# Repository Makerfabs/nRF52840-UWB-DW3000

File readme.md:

# Makerfabs nRF52840 UWB DW3000

**The DW3000 library in this repository was developed by NConcepts, not Makerfabs.  Makerfabs is simply responsible for maintaining the repository.**

## 1.Intruduce

Product Link ：[nRF52840 UWB DW3000](https://www.makerfabs.com/nrf52840-uwb-dw3000.html) 

Wiki Link : [nRF52840 UWB DW3000](https://wiki.makerfabs.com/nRF52840%20DW3000%20UWB.html)

Usage : [one-anchor--one-tag](https://github.com/Makerfabs/nRF52840-UWB-DW3000#31-one-anchor--one-tag)

[multi-anchor--multi-tag](https://github.com/Makerfabs/nRF52840-UWB-DW3000#32-multi-anchor--multi-tag)

## 2.Feature

- Controller: nRF52840, 64 MHz Cortex-M4 with FPU, 1 MB Flash, 256 KB RAM.
- DW3000 UWB module.

## 3. Usage

Download the DW3000 library in [GitHub](https://github.com/Makerfabs/nRF52840-UWB-DW3000/tree/main/Dw3000), and put it to the Arduino library file.

- The default is usually in the "C:\Users\Your username\Documents\Arduino\libraries"

### 3.1 One Anchor + one Tag

- Prepare the module and connect it to the PC with a USB cable.

- Open the Arduino IDE.

- Click **File-->Examples-->DW3000-->Makerfabs_Range_TX**.

- Select the development board “Nordic nRF52840 DK” and the port.

- Upload the sketch to the board.

- Prepare **another module** and connect it to the PC with a USB cable.

- Click **File-->Examples-->DW3000-->Makerfabs_Range_RX**.

- Select the development board “Nordic nRF52840 DK” and the port.

- Upload the sketch to the board.

### 3.2 Multi Anchor + Multi Tag

This is the example to get the distance value from multi Tag to multi Anchor.

The network uses a designated **Master Anchor** to coordinate synchronization and network scheduling.

``` 
#define MASTER_ANCHOR_ID    0xA0
```

The Master Anchor serves as the reference node for the entire UWB network and is responsible for:

- TDMA timing coordination
- Tag scheduling reference
- Maintaining a common network time base

All Anchors and Tags in the network must be configured with the same `MASTER_ANCHOR_ID`.

**Set the board to Anchor X or Tag X**

- Open the Arduino IDE.

- Click **File-->Examples-->DW3000-->Makerfabs_Multi_Anchor_Multi_Tag_Anchor** to open the Anchor code.

- Click **File-->Examples-->DW3000-->Makerfabs_Multi_Anchor_Multi_Tag_Tag** to open the Tag code.

Modify code to get the Anchor or Tag that you want to define

``` 
// 0xA0~0xA7
#define MASTER_ANCHOR_ID    0xA0
```

``` 
//For example 0, 1, 2..
#define TAG_ID              0
```

Use Type-C USB cable to connect the board and PC, and select the development board "Nordic nRF52840 DK" and the port.

Verify the code and upload.

Repeat to set up multiple Anchor and multiple Tag.

Open the port for any anchor to view the distances from all tags to all anchors.

Results for 8Tag + 8anchor

### 3.3UWB Positioning Python Program
You can use Python for UWB positioning. Double-click to open [uwb_visualizer.exe](https://github.com/Makerfabs/Makerfabs-ESP32-UWB-DW3000/tree/main/example/uwb_visualizer).

Set the coordinates for the four anchors, select the serial port for one of them, and click “Start” to begin monitoring.

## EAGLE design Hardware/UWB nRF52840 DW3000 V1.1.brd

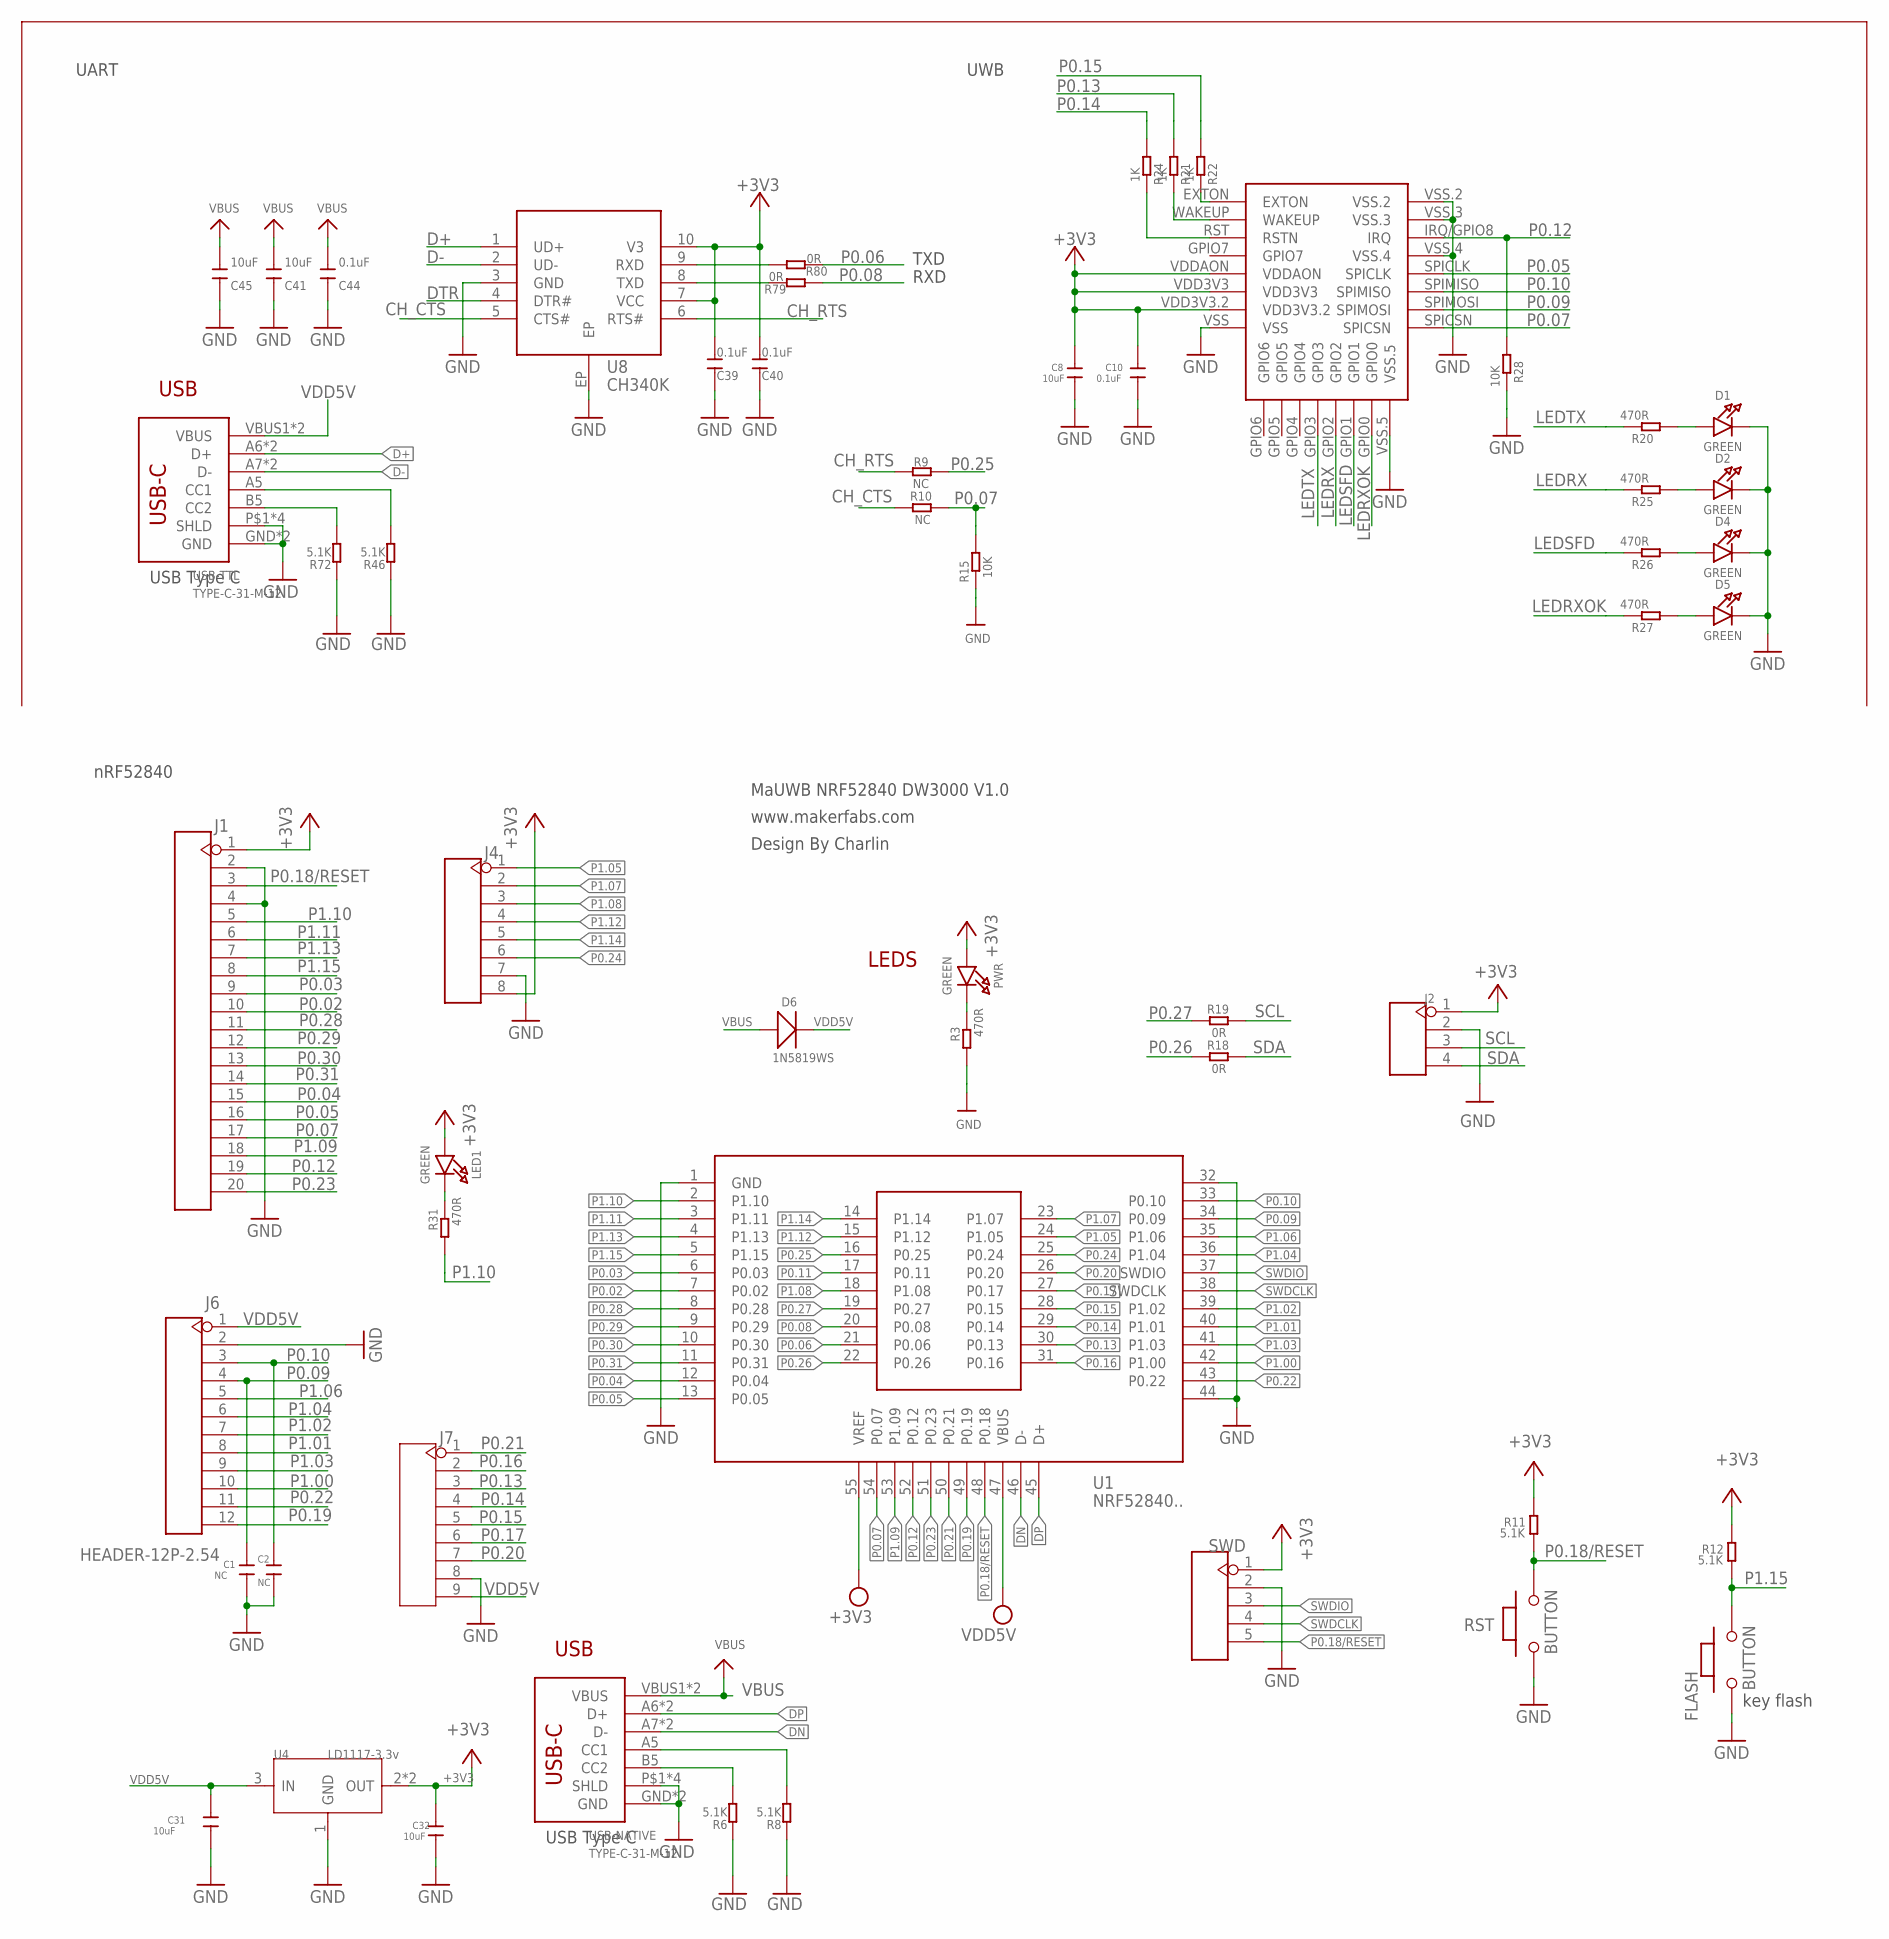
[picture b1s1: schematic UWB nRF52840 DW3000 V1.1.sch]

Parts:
C1, C2: NC; C0603
C8, C31, C32: 10uF; C0603
C10: 0.1uF; C0603
C39, C40, C44: 0.1uF; DISCRETE_C0603
C41, C45: 10uF; DISCRETE_C0603
D1, D2, D4, D5: GREEN; CHIPLED_0805_NOOUTLINE
D6: 1N5819WS; SOD323
FLASH: BUTTON; 157SW
J1: HEADER-20P-2.54; 20P-2.54
J2: HEADER-4P-60/35MILROUND; 4P-65/35ROUND
J4: HEADER-8P-2.54; 8P-2.54
J6: HEADER-12P-2.54; 12P-2.54
J7: HEADER-9P-2.54; 9P-2.54
LED1: GREEN; CHIPLED_0805_NOOUTLINE
PWR: GREEN; CHIPLED_0805_NOOUTLINE
R3, R20, R25, R26, R27, R31: 470R; R0603
R6, R8, R46, R72: 5.1K; DISCRETE_R0603
R9, R10: NC; R0603
R11, R12: 5.1K; R0603
R15, R28: 10K; R0603
R18, R19, R79, R80: 0R; R0603
R21, R22, R24: 1K; R0603
RST: BUTTON; 157SW
SWD: HEADER-5P-2.54; 5P-2.54
U1: NRF52840..
U4: LD1117-3.3v; SOT89
U5: DWM1000
U8: CH340K; ESOP-10-EP-150MIL
USB-NATIVE: TYPE-C-31-M-12
USB-TTL: TYPE-C-31-M-12

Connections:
+3V3: C8.1, C10.1, C32.1, C39.2, C40.2, J1.1, J2.1, J4.8, LED1.A, PWR.A, R11.2, R12.2, SWD.1, U1.55 (VREF), U4.2 (OUT), U4.4 (OUT), U5.VDD3V3, U5.VDD3V3.2, U5.VDDAON, U8.7 (VCC), U8.10 (V3)
CH_CTS: R10.2, U8.5 (CTS#)
CH_RTS: R9.2, U8.6 (RTS#)
D+: U8.1 (UD+), USB-TTL.A6 (D+), USB-TTL.B6 (D+)
D-: U8.2 (UD-), USB-TTL.A7 (D-), USB-TTL.B7 (D-)
DN: U1.46 (D-), USB-NATIVE.A7 (D-), USB-NATIVE.B7 (D-)
DP: U1.45 (D+), USB-NATIVE.A6 (D+), USB-NATIVE.B6 (D+)
DTR: U8.4 (DTR#)
GND: C1.2, C2.2, C8.2, C10.2, C31.2, C32.2, C39.1, C40.1, C41.1, C44.1, C45.1, D1.C, D2.C, D4.C, D5.C, FLASH.1, J1.2, J1.4, J2.2, J4.7, J6.2, J7.8, R3.2, R6.1, R8.1, R15.2, R28.1, R46.1, R72.1, RST.1, SWD.2, U1.1 (GND), U1.32, U1.44, U4.1 (GND), U5.VSS, U5.VSS.2, U5.VSS.3, U5.VSS.4, U5.VSS.5, U8.3 (GND), U8.EP, USB-NATIVE.GND, USB-NATIVE.GND2 (GND), USB-NATIVE.P$1 (SHLD), USB-NATIVE.P$2 (SHLD), USB-NATIVE.P$3 (SHLD), USB-NATIVE.P$4 (SHLD), USB-TTL.GND, USB-TTL.GND2 (GND), USB-TTL.P$1 (SHLD), USB-TTL.P$2 (SHLD), USB-TTL.P$3 (SHLD), USB-TTL.P$4 (SHLD)
LEDRX: R25.1, U5.GPIO2
LEDRXOK: R27.1, U5.GPIO0
LEDSFD: R26.1, U5.GPIO1
LEDTX: R20.1, U5.GPIO3
unnamed: LED1.C, R31.1
unnamed: D1.A, R20.2
unnamed: D2.A, R25.2
unnamed: PWR.C, R3.1
unnamed: D4.A, R26.2
unnamed: D5.A, R27.2
unnamed: R22.1, U5.EXTON
unnamed: R21.1, U5.WAKEUP
unnamed: R24.1, U5.RST (RSTN)
unnamed: R46.2, USB-TTL.A5 (CC1)
unnamed: R72.2, USB-TTL.B5 (CC2)
unnamed: R8.2, USB-NATIVE.A5 (CC1)
unnamed: R6.2, USB-NATIVE.B5 (CC2)
unnamed: R80.2, U8.9 (RXD)
unnamed: R79.2, U8.8 (TXD)
P0.02: J1.10, U1.7 (P0.02)
P0.03: J1.9, U1.6 (P0.03)
P0.04: J1.15, U1.12 (P0.04)
P0.05: J1.16, U1.13 (P0.05), U5.SPICLK
P0.06: R80.1, U1.21 (P0.06)
P0.07: J1.17, R10.1, R15.1, U1.54 (P0.07), U5.SPICSN
P0.08: R79.1, U1.20 (P0.08)
P0.09: C1.1, J6.4, U1.34 (P0.09), U5.SPIMOSI
P0.10: C2.1, J6.3, U1.33 (P0.10), U5.SPIMISO
P0.11: U1.17 (P0.11)
P0.12: J1.19, R28.2, U1.52 (P0.12), U5.IRQ/GPIO8 (IRQ)
P0.13: J7.3, R21.2, U1.30 (P0.13)
P0.14: J7.4, R24.2, U1.29 (P0.14)
P0.15: J7.5, R22.2, U1.28 (P0.15)
P0.16: J7.2, U1.31 (P0.16)
P0.17: J7.6, U1.27 (P0.17)
P0.18/RESET: J1.3, R11.1, RST.2, SWD.5, U1.48 (P0.18)
P0.19: J6.12, U1.49 (P0.19)
P0.20: J7.7, U1.26 (P0.20)
P0.21: J7.1, U1.50 (P0.21)
P0.22: J6.11, U1.43 (P0.22)
P0.23: J1.20, U1.51 (P0.23)
P0.24: J4.6, U1.25 (P0.24)
P0.25: R9.1, U1.16 (P0.25)
P0.26: R18.2, U1.22 (P0.26)
P0.27: R19.2, U1.19 (P0.27)
P0.28: J1.11, U1.8 (P0.28)
P0.29: J1.12, U1.9 (P0.29)
P0.30: J1.13, U1.10 (P0.30)
P0.31: J1.14, U1.11 (P0.31)
P1.00: J6.10, U1.42 (P1.00)
P1.01: J6.8, U1.40 (P1.01)
P1.02: J6.7, U1.39 (P1.02)
P1.03: J6.9, U1.41 (P1.03)
P1.04: J6.6, U1.36 (P1.04)
P1.05: J4.1, U1.24 (P1.05)
P1.06: J6.5, U1.35 (P1.06)
P1.07: J4.2, U1.23 (P1.07)
P1.08: J4.3, U1.18 (P1.08)
P1.09: J1.18, U1.53 (P1.09)
P1.10: J1.5, R31.2, U1.2 (P1.10)
P1.11: J1.6, U1.3 (P1.11)
P1.12: J4.4, U1.15 (P1.12)
P1.13: J1.7, U1.4 (P1.13)
P1.14: J4.5, U1.14 (P1.14)
P1.15: FLASH.2, J1.8, R12.1, U1.5 (P1.15)
SCL: J2.3, R19.1
SDA: J2.4, R18.1
SWDCLK: SWD.4, U1.38 (SWDCLK)
SWDIO: SWD.3, U1.37 (SWDIO)
VBUS: C41.2, C44.2, C45.2, D6.+, USB-NATIVE.VBUS1 (VBUS), USB-NATIVE.VBUS2 (VBUS)
VDD5V: C31.1, D6.-, J6.1, J7.9, U1.47 (VBUS), U4.3 (IN), USB-TTL.VBUS1 (VBUS), USB-TTL.VBUS2 (VBUS)

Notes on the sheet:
LEDS
key flash
MaUWB NRF52840 DW3000 V1.0
www.makerfabs.com
Design By Charlin
USB
USB Type C
RXD
TXD
UART
UWB
nRF52840

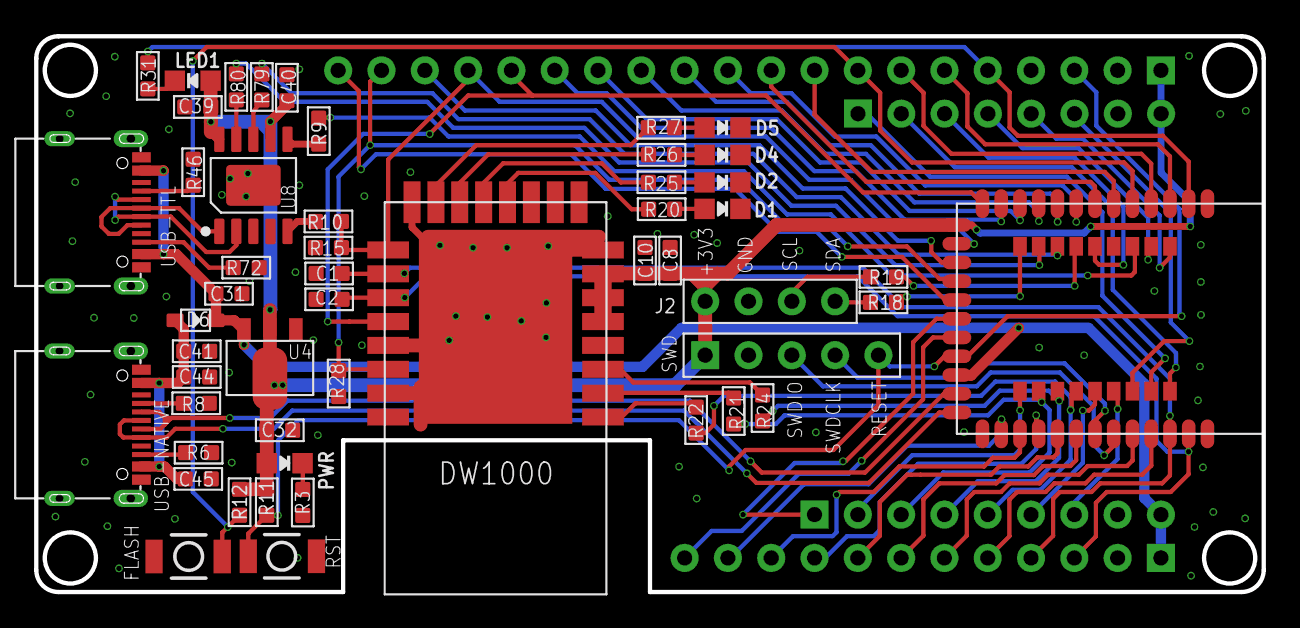
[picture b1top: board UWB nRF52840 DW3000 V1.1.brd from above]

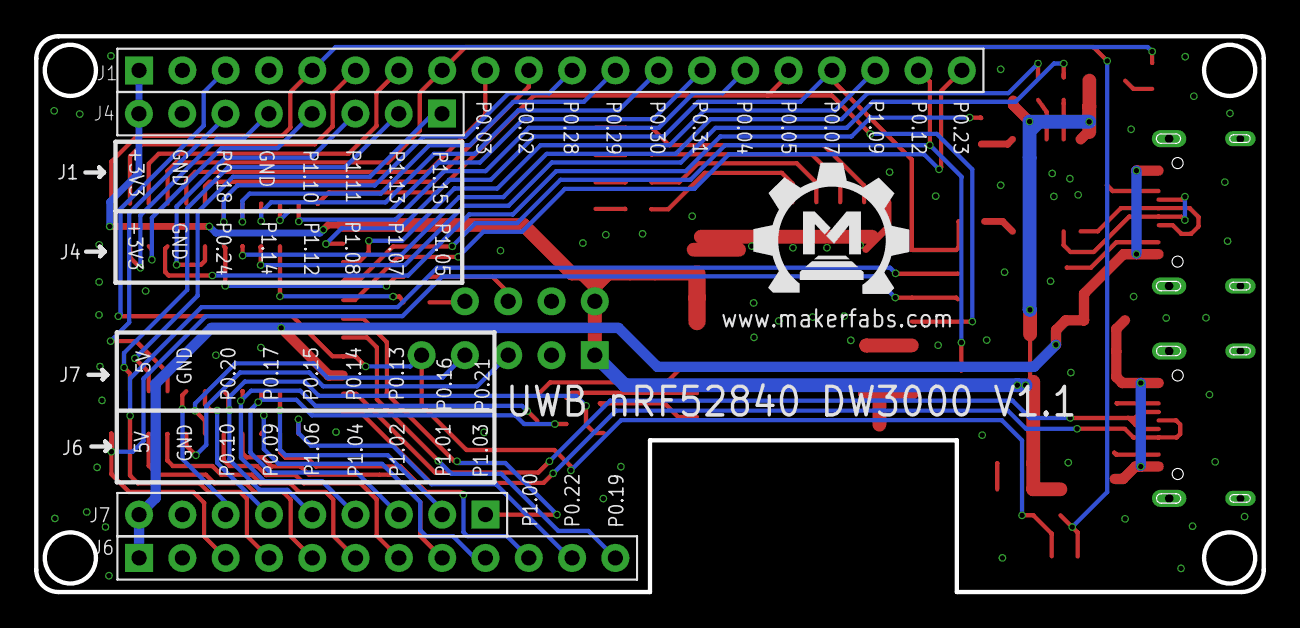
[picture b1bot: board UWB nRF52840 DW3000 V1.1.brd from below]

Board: 2 copper layers, 72.0 x 32.6 mm, 56 parts (5 on the bottom side), 78 nets.

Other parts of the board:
U$1: MAKERFABS_0.3

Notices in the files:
parts and their libraries:
microbuilder: This work is placed in the public domain, and may be freely used for commercial and non-commercial work with the following conditions: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
SparkFun-Aesthetics: Licensing: Creative Commons ShareAlike 4.0 International - https://creativecommons.org/licenses/by-sa/4.0
